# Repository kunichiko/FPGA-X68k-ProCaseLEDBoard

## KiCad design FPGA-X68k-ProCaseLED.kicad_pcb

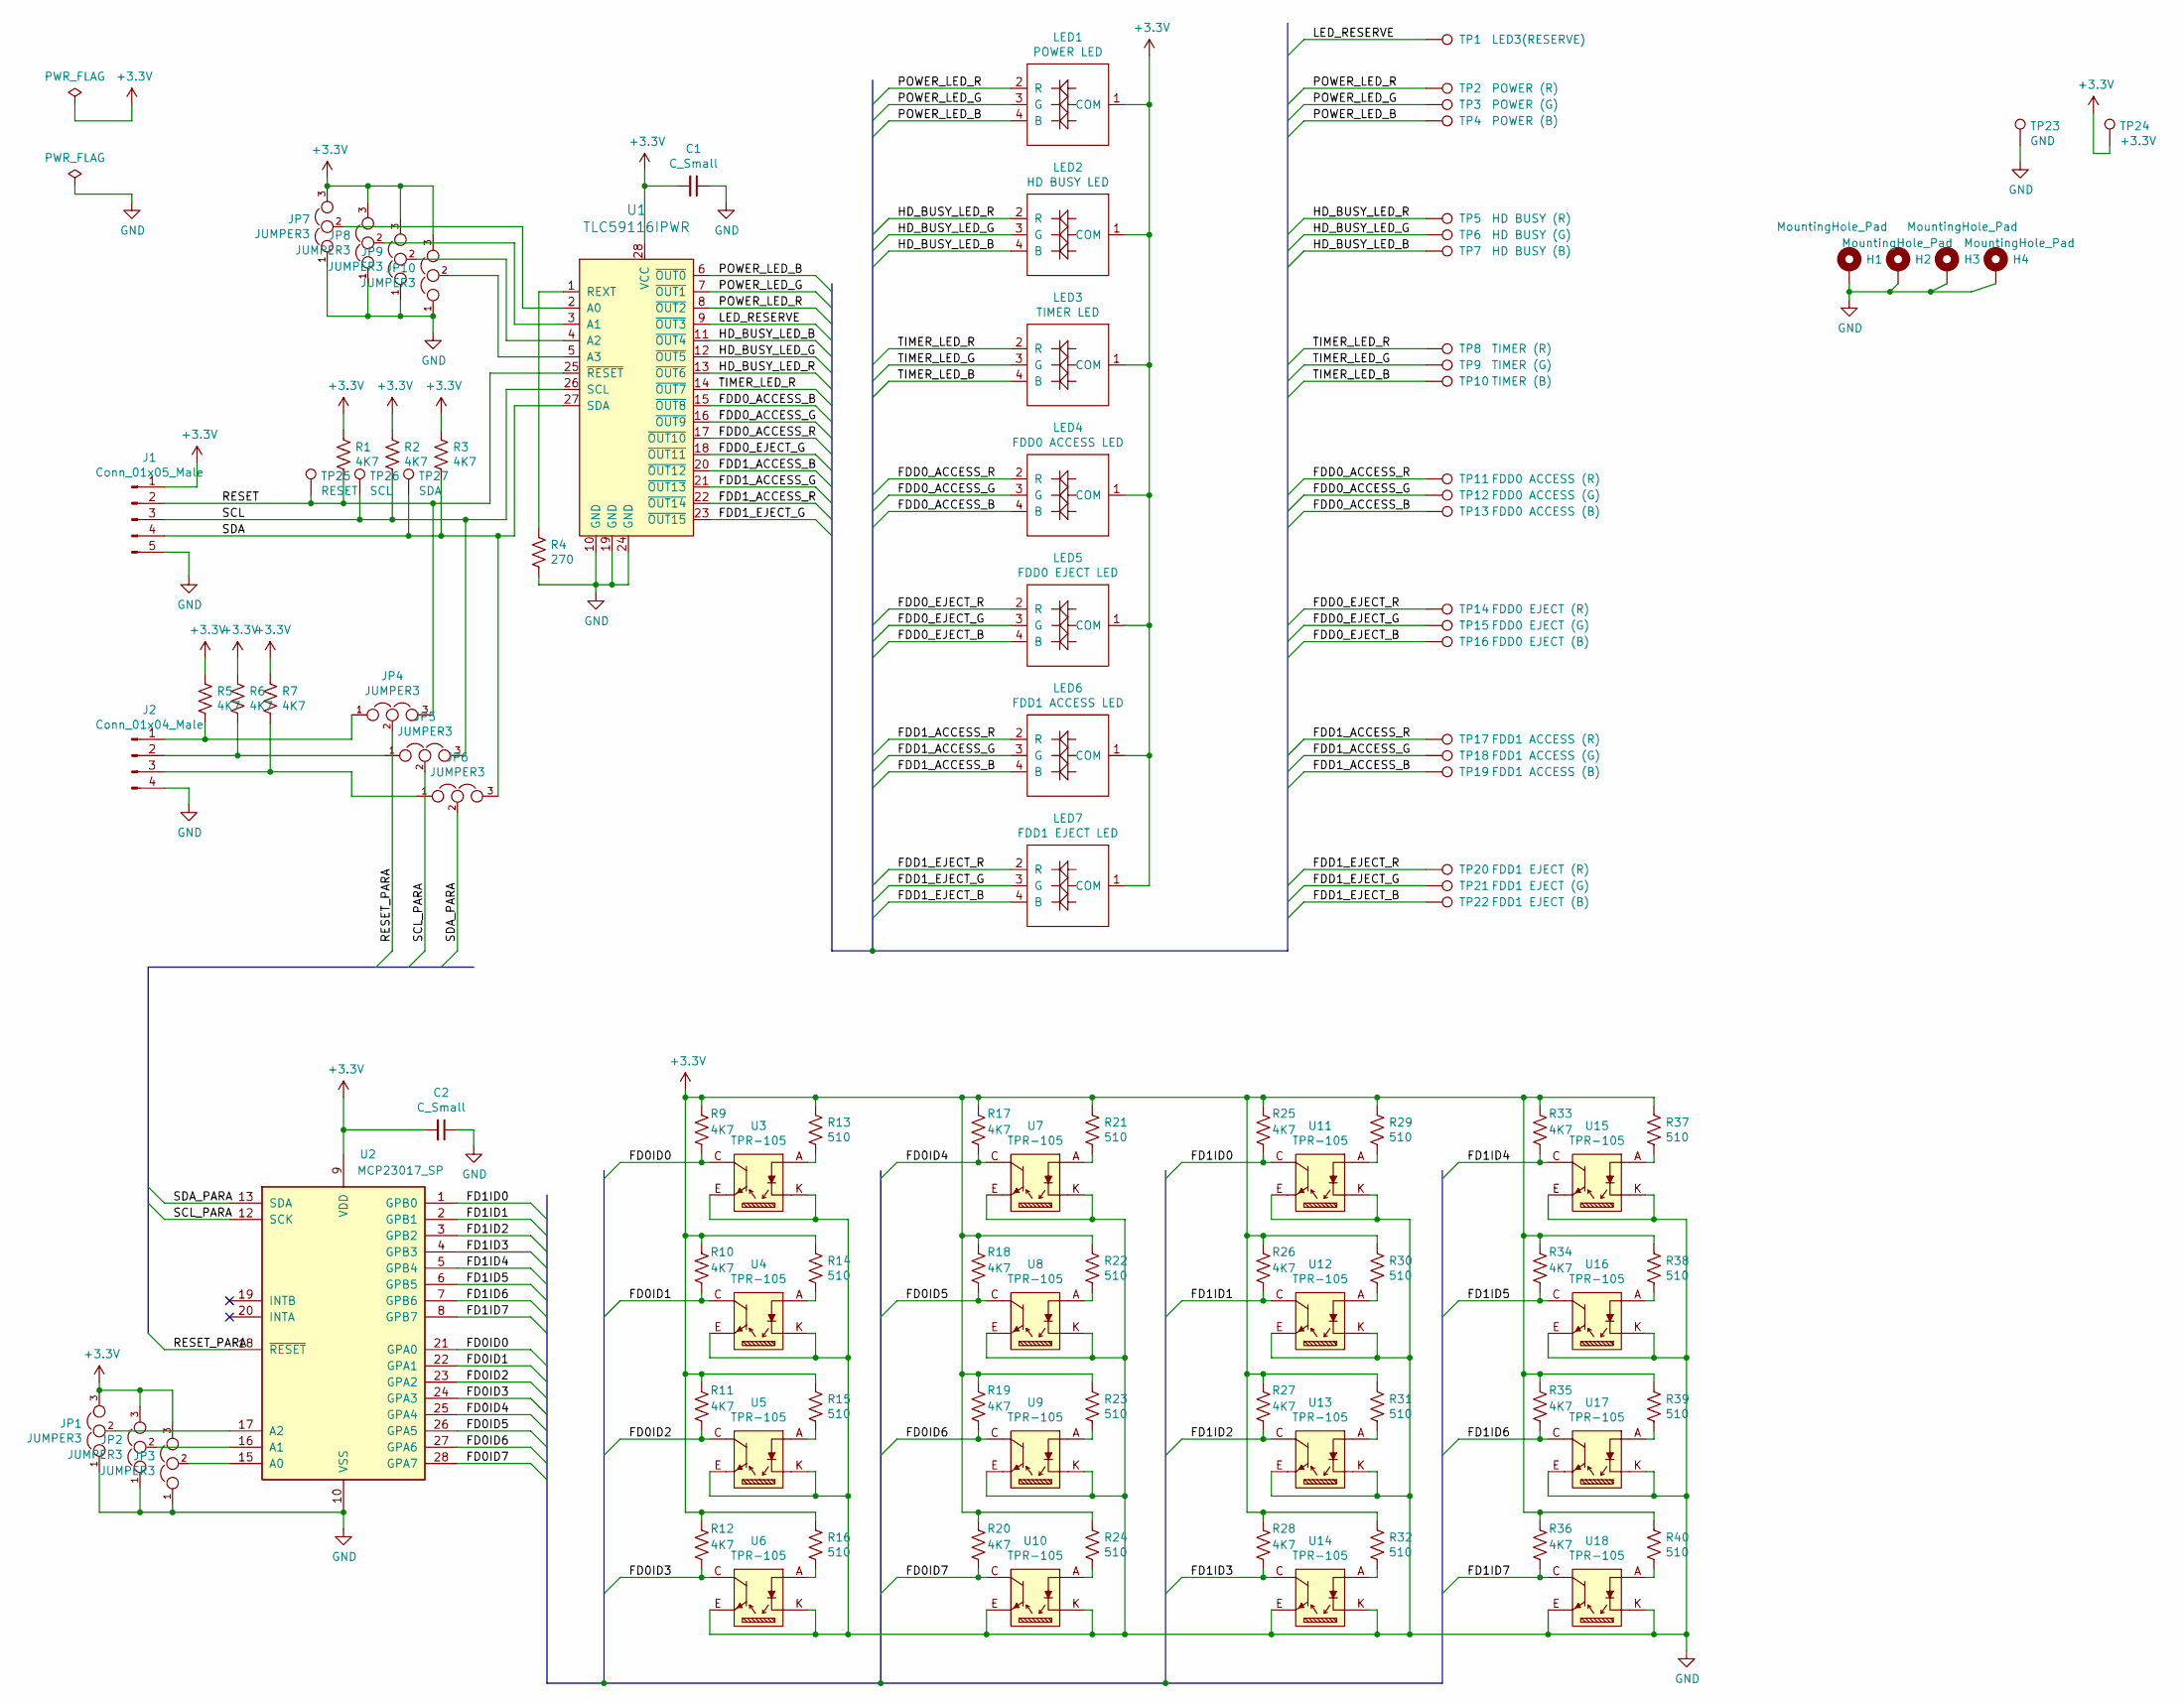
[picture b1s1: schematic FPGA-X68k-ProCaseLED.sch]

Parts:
C1, C2: C_Small; C_0603_1608Metric_Pad1.05x0.95mm_HandSolder
H1, H2, H3, H4: MountingHole_Pad; MountingHole_3.2mm_M3_Pad
J1: Conn_01x05_Male; JST_EH_S5B-EH_1x05_P2.50mm_Horizontal
J2: Conn_01x04_Male; JST_EH_S4B-EH_1x04_P2.50mm_Horizontal
JP1, JP2, JP3, JP4, JP5, JP6, JP7, JP8, JP9, JP10: JUMPER3; SolderJumper-3_P1.3mm_Open_RoundedPad1.0x1.5mm_NumberLabels
LED1: POWER LED; Full-color LED LTSN-B32JEGBB-LY
LED2: HD BUSY LED; Full-color LED LTSN-B32JEGBB-LY
LED3: TIMER LED; Full-color LED LTSN-B32JEGBB-LY
LED4: FDD0 ACCESS LED; Full-color LED LTSN-B32JEGBB-LY
LED5: FDD0 EJECT LED; Full-color LED LTSN-B32JEGBB-LY
LED6: FDD1 ACCESS LED; Full-color LED LTSN-B32JEGBB-LY
LED7: FDD1 EJECT LED; Full-color LED LTSN-B32JEGBB-LY
R1, R2, R3, R5, R6, R7, R9, R10, R11, R12, R17, R18, R19, R20, R25, R26, R27, R28, R33, R34, R35, R36: 4K7; R_0603_1608Metric_Pad1.05x0.95mm_HandSolder
R4: 270; R_0603_1608Metric_Pad1.05x0.95mm_HandSolder
R13, R14, R15, R16, R21, R22, R23, R24, R29, R30, R31, R32, R37, R38, R39, R40: 510; R_0603_1608Metric_Pad1.05x0.95mm_HandSolder
TP1: LED3(RESERVE); TestPoint_Pad_1.0x1.0mm
TP2: POWER (R); TestPoint_Pad_1.0x1.0mm
TP3: POWER (G); TestPoint_Pad_1.0x1.0mm
TP4: POWER (B); TestPoint_Pad_1.0x1.0mm
TP5: HD BUSY (R); TestPoint_Pad_1.0x1.0mm
TP6: HD BUSY (G); TestPoint_Pad_1.0x1.0mm
TP7: HD BUSY (B); TestPoint_Pad_1.0x1.0mm
TP8: TIMER (R); TestPoint_Pad_1.0x1.0mm
TP9: TIMER (G); TestPoint_Pad_1.0x1.0mm
TP10: TIMER (B); TestPoint_Pad_1.0x1.0mm
TP11: FDD0 ACCESS (R); TestPoint_Pad_1.0x1.0mm
TP12: FDD0 ACCESS (G); TestPoint_Pad_1.0x1.0mm
TP13: FDD0 ACCESS (B); TestPoint_Pad_1.0x1.0mm
TP14: FDD0 EJECT (R); TestPoint_Pad_1.0x1.0mm
TP15: FDD0 EJECT (G); TestPoint_Pad_1.0x1.0mm
TP16: FDD0 EJECT (B); TestPoint_Pad_1.0x1.0mm
TP17: FDD1 ACCESS (R); TestPoint_Pad_1.0x1.0mm
TP18: FDD1 ACCESS (G); TestPoint_Pad_1.0x1.0mm
TP19: FDD1 ACCESS (B); TestPoint_Pad_1.0x1.0mm
TP20: FDD1 EJECT (R); TestPoint_Pad_1.0x1.0mm
TP21: FDD1 EJECT (G); TestPoint_Pad_1.0x1.0mm
TP22: FDD1 EJECT (B); TestPoint_Pad_1.0x1.0mm
TP23: GND; TestPoint_THTPad_D1.5mm_Drill0.7mm
TP24: +3.3V; TestPoint_THTPad_D1.5mm_Drill0.7mm
TP25: RESET; TestPoint_THTPad_D1.5mm_Drill0.7mm
TP26: SCL; TestPoint_THTPad_D1.5mm_Drill0.7mm
TP27: SDA; TestPoint_THTPad_D1.5mm_Drill0.7mm
U1: TLC59116IPWR; TSSOP-28_W4.40mm; MPN TLC59116IPWR; Digi-Key_PN 296-23354-1-ND
U2: MCP23017_SP; DIP-28_W7.62mm
U3, U4, U5, U6, U7, U8, U9, U10, U11, U12, U13, U14, U15, U16, U17, U18: TPR-105

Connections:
+3V3: C1.2, C2.2, J1.1, JP1.3, JP2.3, JP3.3, JP7.3, JP8.3, JP9.3, JP10.3, LED1.1 (COM), LED2.1 (COM), LED3.1 (COM), LED4.1 (COM), LED5.1 (COM), LED6.1 (COM), LED7.1 (COM), R1.2, R2.2, R3.2, R5.2, R6.2, R7.2, R9.2, R10.2, R11.2, R12.2, R13.2, R14.2, R15.2, R16.2, R17.2, R18.2, R19.2, R20.2, R21.2, R22.2, R23.2, R24.2, R25.2, R26.2, R27.2, R28.2, R29.2, R30.2, R31.2, R32.2, R33.2, R34.2, R35.2, R36.2, R37.2, R38.2, R39.2, R40.2, TP24.1, U1.28 (VCC), U2.9 (VDD)
/FD0ID0: R9.1, U2.21 (GPA0), U3.C
/FD0ID1: R10.1, U2.22 (GPA1), U4.C
/FD0ID2: R11.1, U2.23 (GPA2), U5.C
/FD0ID3: R12.1, U2.24 (GPA3), U6.C
/FD0ID4: R17.1, U2.25 (GPA4), U7.C
/FD0ID5: R18.1, U2.26 (GPA5), U8.C
/FD0ID6: R19.1, U2.27 (GPA6), U9.C
/FD0ID7: R20.1, U2.28 (GPA7), U10.C
/FD1ID0: R25.1, U2.1 (GPB0), U11.C
/FD1ID1: R26.1, U2.2 (GPB1), U12.C
/FD1ID2: R27.1, U2.3 (GPB2), U13.C
/FD1ID3: R28.1, U2.4 (GPB3), U14.C
/FD1ID4: R33.1, U2.5 (GPB4), U15.C
/FD1ID5: R34.1, U2.6 (GPB5), U16.C
/FD1ID6: R35.1, U2.7 (GPB6), U17.C
/FD1ID7: R36.1, U2.8 (GPB7), U18.C
/FDD0_ACCESS_B: LED4.4 (B), TP13.1, U1.15 (~OUT8)
/FDD0_ACCESS_G: LED4.3 (G), TP12.1, U1.16 (~OUT9)
/FDD0_ACCESS_R: LED4.2 (R), TP11.1, U1.17 (~OUT10)
/FDD0_EJECT_B: LED5.4 (B), TP16.1
/FDD0_EJECT_G: LED5.3 (G), TP15.1, U1.18 (~OUT11)
/FDD0_EJECT_R: LED5.2 (R), TP14.1
/FDD1_ACCESS_B: LED6.4 (B), TP19.1, U1.20 (~OUT12)
/FDD1_ACCESS_G: LED6.3 (G), TP18.1, U1.21 (~OUT13)
/FDD1_ACCESS_R: LED6.2 (R), TP17.1, U1.22 (~OUT14)
/FDD1_EJECT_B: LED7.4 (B), TP22.1
/FDD1_EJECT_G: LED7.3 (G), TP21.1, U1.23 (~OUT15)
/FDD1_EJECT_R: LED7.2 (R), TP20.1
/HD_BUSY_LED_B: LED2.4 (B), TP7.1, U1.11 (~OUT4)
/HD_BUSY_LED_G: LED2.3 (G), TP6.1, U1.12 (~OUT5)
/HD_BUSY_LED_R: LED2.2 (R), TP5.1, U1.13 (~OUT6)
/LED_RESERVE: TP1.1, U1.9 (~OUT3)
/POWER_LED_B: LED1.4 (B), TP4.1, U1.6 (~OUT0)
/POWER_LED_G: LED1.3 (G), TP3.1, U1.7 (~OUT1)
/POWER_LED_R: LED1.2 (R), TP2.1, U1.8 (~OUT2)
/RESET: J1.2, JP4.3, R1.1, TP25.1, U1.25 (~RESET)
/RESET_PARA: JP4.2, U2.18 (~RESET~)
/SCL: J1.3, JP5.3, R2.1, TP26.1, U1.26 (SCL)
/SCL_PARA: JP5.2, U2.12 (SCK)
/SDA: J1.4, JP6.3, R3.1, TP27.1, U1.27 (SDA)
/SDA_PARA: JP6.2, U2.13 (SDA)
/TIMER_LED_B: LED3.4 (B), TP10.1
/TIMER_LED_G: LED3.3 (G), TP9.1
/TIMER_LED_R: LED3.2 (R), TP8.1, U1.14 (~OUT7)
GND: C1.1, C2.1, H1.1, H2.1, H3.1, H4.1, J1.5, J2.4, JP1.1, JP2.1, JP3.1, JP7.1, JP8.1, JP9.1, JP10.1, R4.1, TP23.1, U1.10 (GND), U1.19 (GND), U1.24 (GND), U2.10 (VSS), U3.E, U3.K, U4.E, U4.K, U5.E, U5.K, U6.E, U6.K, U7.E, U7.K, U8.E, U8.K, U9.E, U9.K, U10.E, U10.K, U11.E, U11.K, U12.E, U12.K, U13.E, U13.K, U14.E, U14.K, U15.E, U15.K, U16.E, U16.K, U17.E, U17.K, U18.E, U18.K
unnamed: J2.1, JP4.1, R5.1
unnamed: J2.2, JP5.1, R6.1
unnamed: J2.3, JP6.1, R7.1
unnamed: JP1.2, U2.17 (A2)
unnamed: JP2.2, U2.16 (A1)
unnamed: JP3.2, U2.15 (A0)
unnamed: JP7.2, U1.2 (A0)
unnamed: JP8.2, U1.3 (A1)
unnamed: JP9.2, U1.4 (A2)
unnamed: JP10.2, U1.5 (A3)
unnamed: R4.2, U1.1 (REXT)
unnamed: R13.1, U3.A
unnamed: R14.1, U4.A
unnamed: R15.1, U5.A
unnamed: R16.1, U6.A
unnamed: R21.1, U7.A
unnamed: R22.1, U8.A
unnamed: R23.1, U9.A
unnamed: R24.1, U10.A
unnamed: R29.1, U11.A
unnamed: R30.1, U12.A
unnamed: R31.1, U13.A
unnamed: R32.1, U14.A
unnamed: R37.1, U15.A
unnamed: R38.1, U16.A
unnamed: R39.1, U17.A
unnamed: R40.1, U18.A

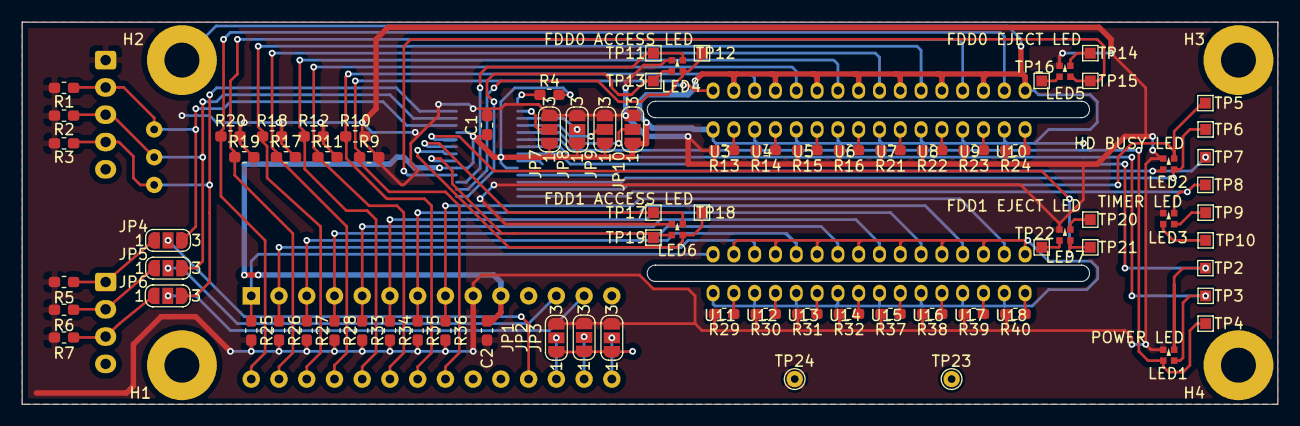
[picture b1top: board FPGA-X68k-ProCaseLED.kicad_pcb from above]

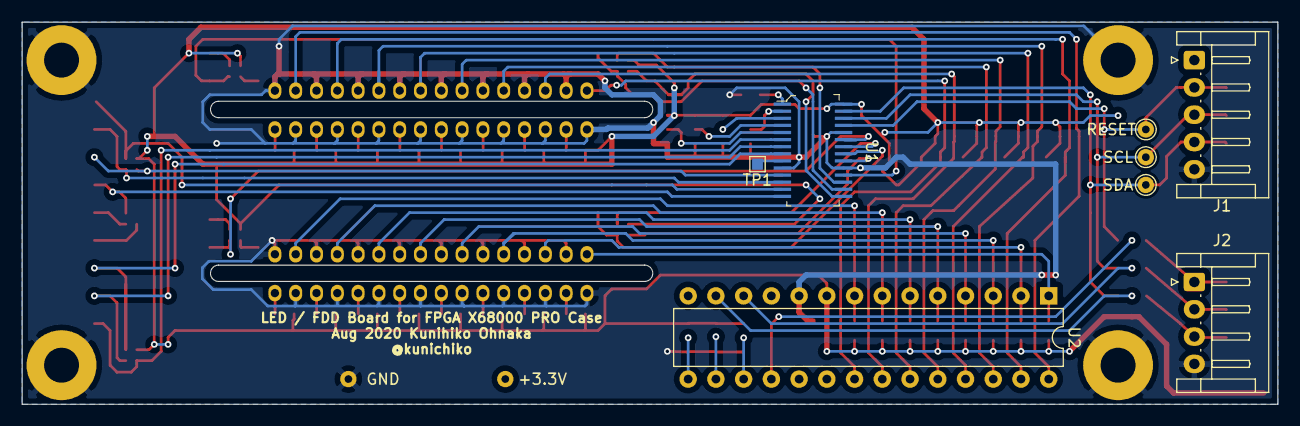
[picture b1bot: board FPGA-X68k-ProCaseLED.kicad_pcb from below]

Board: 2 copper layers, 115.0 x 35.0 mm, 109 parts (8 on the bottom side), 73 nets.

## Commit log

2020-08-02 Add 'digikey-kicad-library' and ' kicad-gigalib' as submodules.
2020-08-08 Initial version.
2020-08-21 First version
2020-08-22 Add miniature FDD sensor circuit.
2020-08-24 Fix the direction of TPR-105.
2020-08-24 Add Fusion PCB order data (gerber and drill).
2020-09-06 Fix LTSN-B32JEGBB-LY's footprint and TIMER LED pattern.
